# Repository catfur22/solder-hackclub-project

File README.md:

# solder-hackclub-project
This is a sans themed pcb that im making. It has a cool silkscreen and custom shape to recreate the character sans from Undertale. It has a led for an eye and when a button is held it makes it flash on and off. I am making this to learn how to use kicad for later projects and also how to make circuits without a microcontroller.

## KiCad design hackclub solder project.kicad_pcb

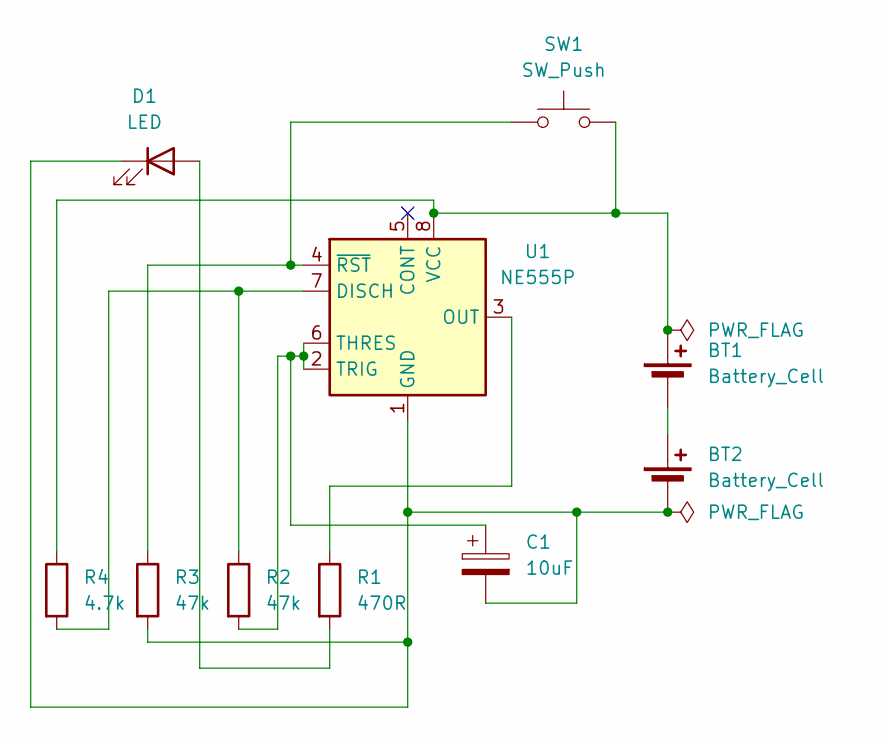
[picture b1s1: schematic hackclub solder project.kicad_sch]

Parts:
BT1, BT2: Battery_Cell; BatteryHolder_Keystone_3034_1x20mm
C1: 10uF; CP_Radial_D8.0mm_P5.00mm
D1: LED; LED_D5.0mm
R1: 470R; R_Axial_DIN0207_L6.3mm_D2.5mm_P7.62mm_Horizontal
R2, R3: 47k; R_Axial_DIN0207_L6.3mm_D2.5mm_P7.62mm_Horizontal
R4: 4.7k; R_Axial_DIN0207_L6.3mm_D2.5mm_P7.62mm_Horizontal
SW1: SW_Push; SW_PUSH_6mm
U1: NE555P; DIP-8_W7.62mm

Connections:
unnamed: BT1.1 (+), R4.1, SW1.2, U1.8 (VCC)
unnamed: BT1.2 (-), BT2.1 (+)
unnamed: BT2.2 (-), C1.2, D1.1 (K), R3.2, U1.1 (GND)
unnamed: D1.2 (A), R1.2
unnamed: R2.1, R4.2, U1.7 (DISCH)
unnamed: R1.1, U1.3 (OUT)
unnamed: C1.1, R2.2, U1.2 (TRIG), U1.6 (THRES)
unnamed: R3.1, SW1.1, U1.4 (~RST)

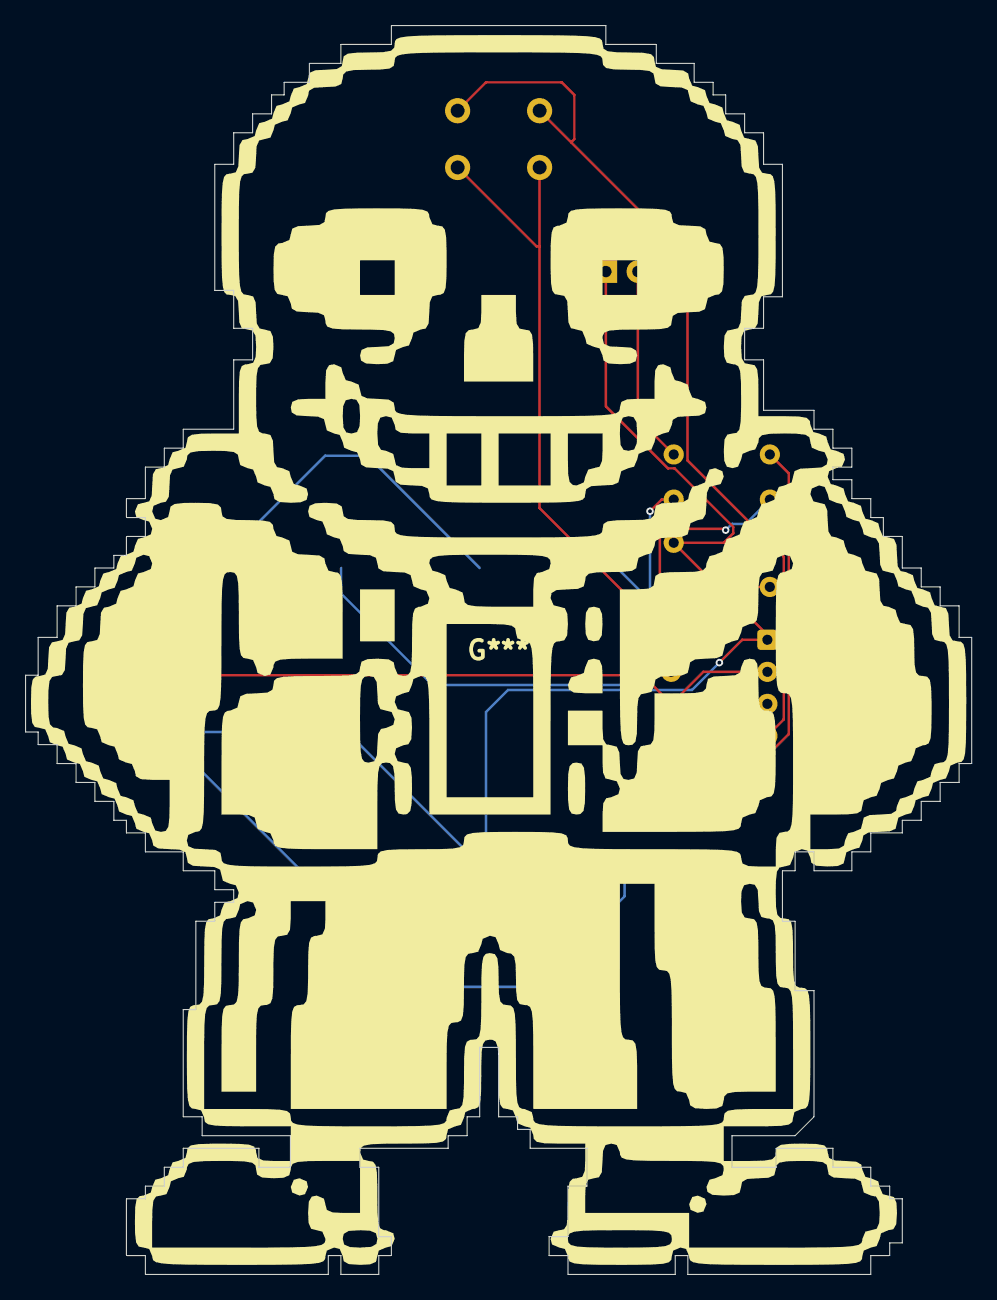
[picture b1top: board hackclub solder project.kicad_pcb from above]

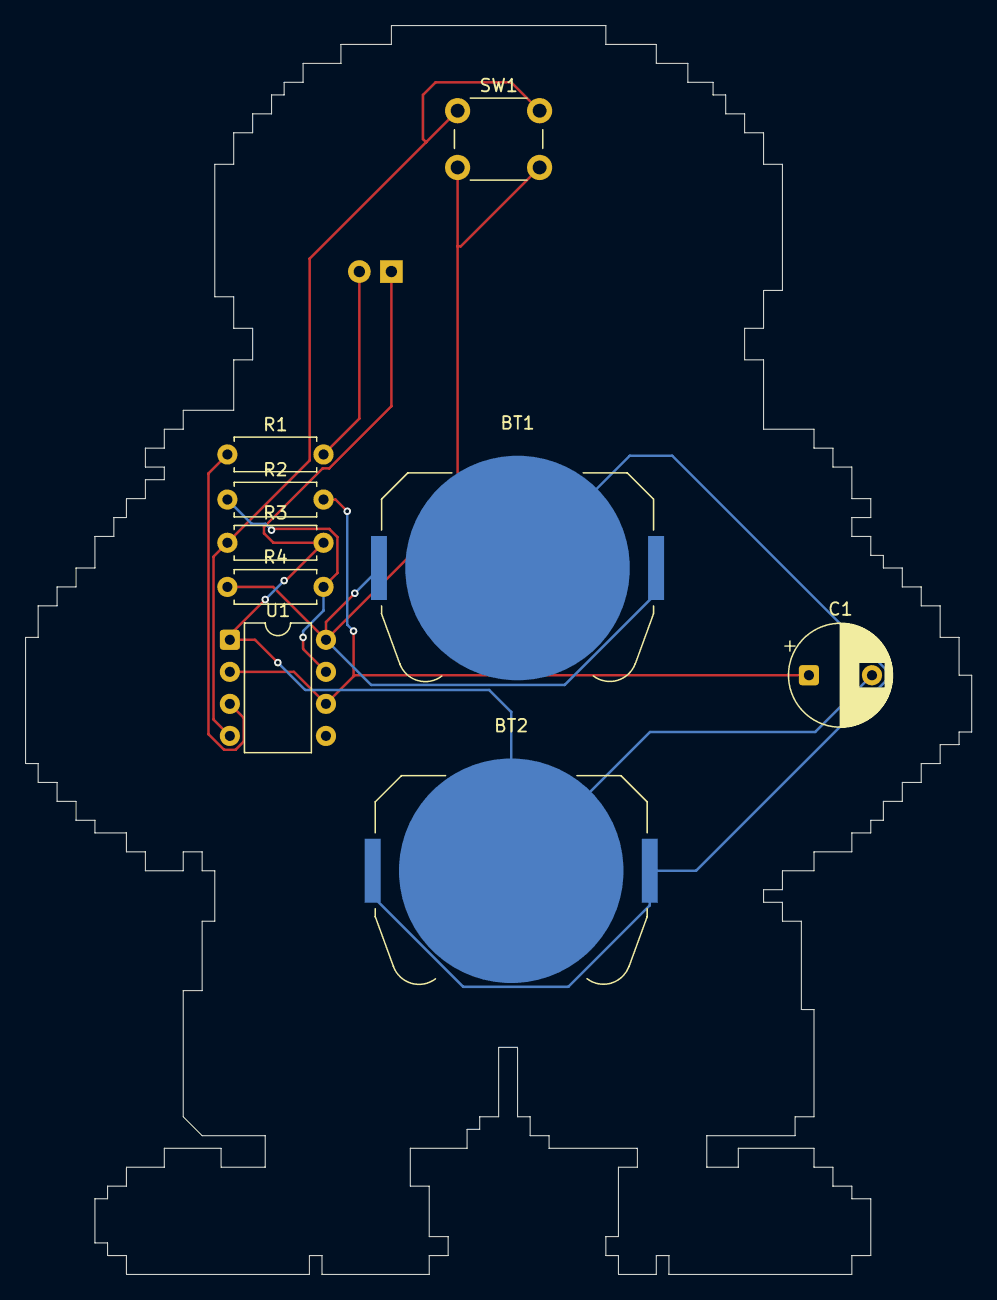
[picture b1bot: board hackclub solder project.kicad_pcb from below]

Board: 2 copper layers, 75.0 x 99.0 mm, 10 parts (9 on the bottom side), 8 nets.
